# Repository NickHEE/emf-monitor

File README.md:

# emf-monitor
BCIT Capstone Project - BC Hydro

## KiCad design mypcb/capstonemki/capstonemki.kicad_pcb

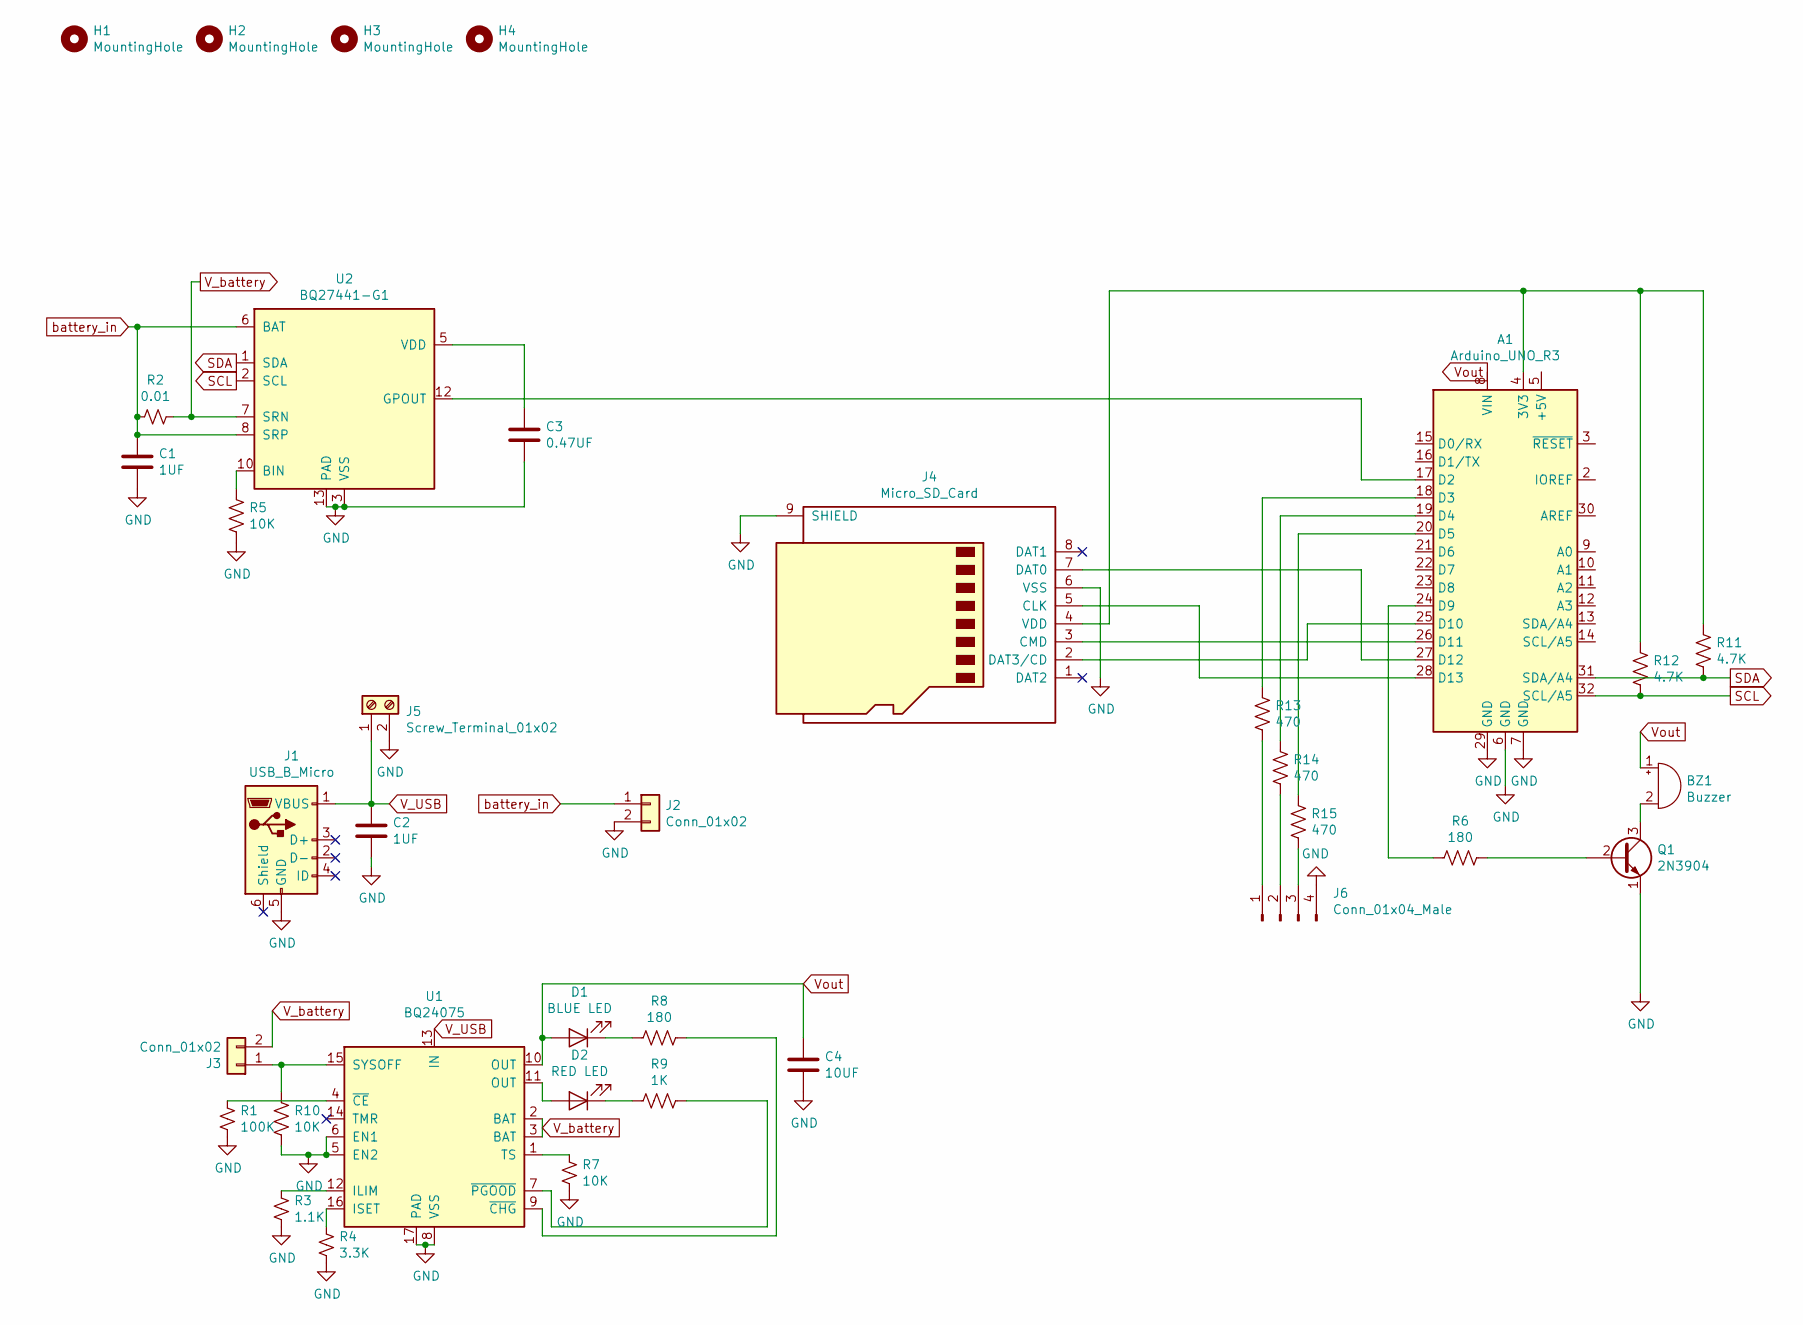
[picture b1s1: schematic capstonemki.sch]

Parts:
A1: Arduino_UNO_R3
BZ1: Buzzer; MagneticBuzzer_ProSignal_ABT-410-RC
C1, C2: 1UF; C_0603_1608Metric
C3: 0.47UF; C_0603_1608Metric
C4: 10UF; C_0603_1608Metric
D1: BLUE LED; LED_0603_1608Metric
D2: RED LED; LED_0603_1608Metric
H1, H2, H3, H4: MountingHole; MountingHole_2.2mm_M2
J1: USB_B_Micro; USB_Micro-B_Molex-105017-0001
J2: Conn_01x02; JST_PH_B2B-PH-K_1x02_P2.00mm_Vertical
J3: Conn_01x02; PinHeader_1x02_P2.54mm_Vertical
J4: Micro_SD_Card; microSD_HC_Molex_104031-0811
J5: Screw_Terminal_01x02; TerminalBlock_bornier-2_P5.08mm
J6: Conn_01x04_Male; PinHeader_1x04_P2.54mm_Vertical
Q1: 2N3904; TO-92_Inline
R1: 100K; R_0603_1608Metric
R2: 0.01; R_0603_1608Metric
R3: 1.1K; R_0603_1608Metric
R4: 3.3K; R_0603_1608Metric
R5, R7, R10: 10K; R_0603_1608Metric
R6, R8: 180; R_0603_1608Metric
R9: 1K; R_0603_1608Metric
R11, R12: 4.7K; R_0603_1608Metric
R13, R14, R15: 470; R_Axial_DIN0309_L9.0mm_D3.2mm_P12.70mm_Horizontal
U1: BQ24075; QFN-16-1EP_3x3mm_P0.5mm_EP1.7x1.7mm
U2: BQ27441-G1; Texas_S-PDSO-N12

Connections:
GND: A1.6 (GND), A1.7 (GND), A1.29 (GND), C1.2, C2.2, C3.2, C4.2, J1.5 (GND), J2.2, J4.6 (VSS), J4.9 (SHIELD), J5.2, J6.4, Q1.1 (E), R1.2, R3.2, R4.2, R5.2, R7.2, R10.2, U1.5 (EN2), U1.6 (EN1), U1.8 (VSS), U1.17 (PAD), U2.3 (VSS), U2.13 (PAD)
unnamed: A1.4 (3V3), J4.4 (VDD), R11.1, R12.2
unnamed: A1.17 (D2), U2.12 (GPOUT)
unnamed: A1.18 (D3), R13.1
unnamed: A1.19 (D4), R14.1
unnamed: A1.20 (D5), R15.1
unnamed: A1.24 (D9), R6.2
unnamed: A1.25 (D10), J4.2 (DAT3/CD)
unnamed: A1.26 (D11), J4.3 (CMD)
unnamed: A1.27 (D12), J4.7 (DAT0)
unnamed: A1.28 (D13), J4.5 (CLK)
unnamed: BZ1.2 (+), Q1.3 (C)
unnamed: C3.1, U2.5 (VDD)
unnamed: D1.1 (K), R8.2
unnamed: D2.1 (K), R9.2
unnamed: D2.2 (A), U1.11 (OUT)
unnamed: J3.1, R10.1, U1.15 (SYSOFF)
unnamed: J6.1, R13.2
unnamed: J6.2, R14.2
unnamed: J6.3, R15.2
unnamed: Q1.2 (B), R6.1
unnamed: R1.1, U1.4 (~CE)
unnamed: R3.1, U1.12 (ILIM)
unnamed: R4.1, U1.16 (ISET)
unnamed: R5.1, U2.10 (BIN)
unnamed: R7.1, U1.1 (TS)
unnamed: R8.1, U1.9 (~CHG)
unnamed: R9.1, U1.7 (~PGOOD)
SCL: A1.32 (SCL/A5), R12.1, U2.2 (SCL)
SDA: A1.31 (SDA/A4), R11.2, U2.1 (SDA)
V_USB: C2.1, J1.1 (VBUS), J5.1, U1.13 (IN)
V_battery: J3.2, R2.1, U1.2 (BAT), U1.3 (BAT), U2.7 (SRN)
Vout: A1.8 (VIN), BZ1.1 (-), C4.1, D1.2 (A), U1.10 (OUT)
battery_in: C1.1, J2.1, R2.2, U2.6 (BAT), U2.8 (SRP)

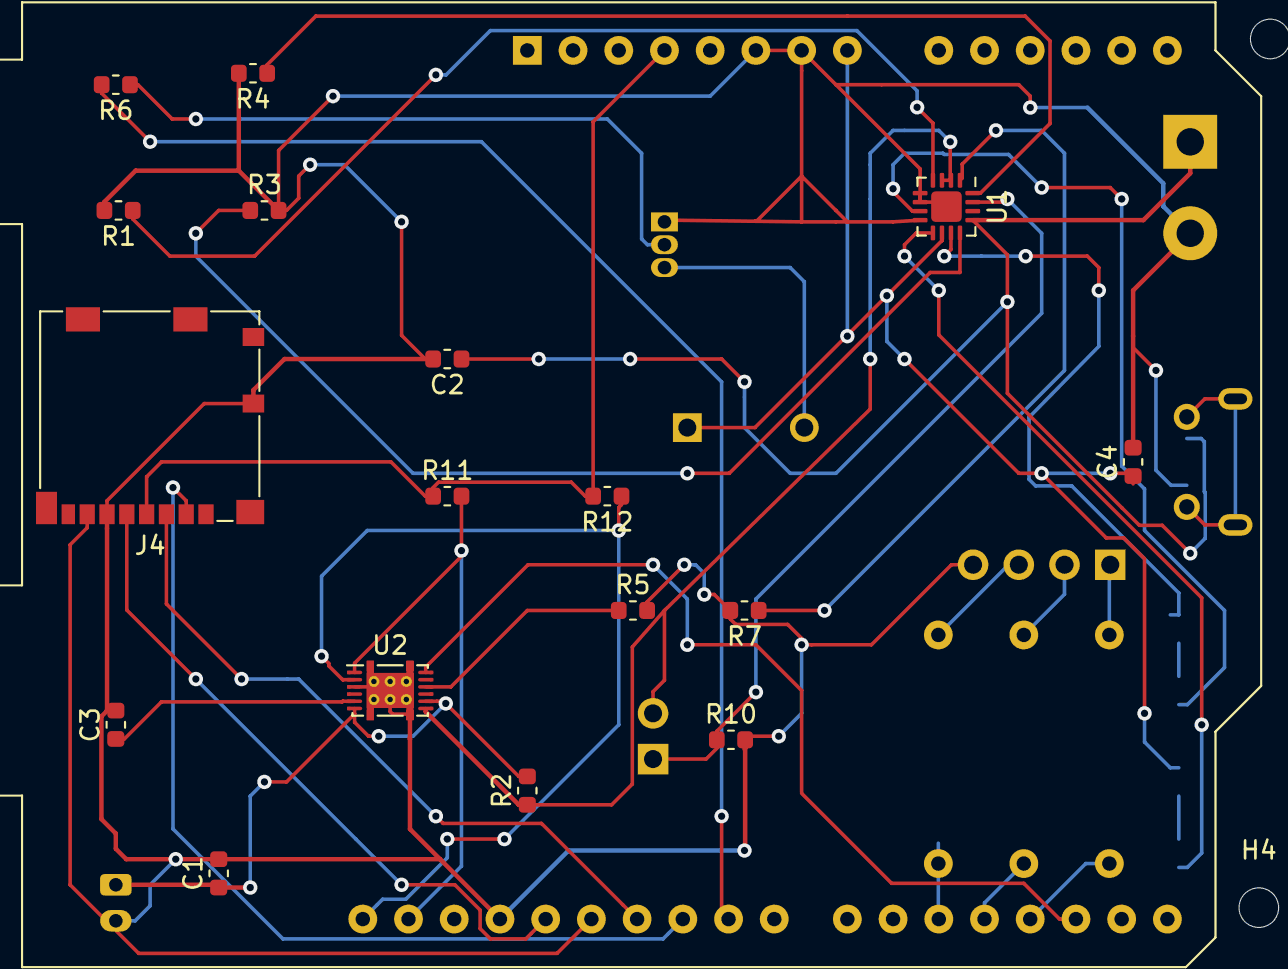
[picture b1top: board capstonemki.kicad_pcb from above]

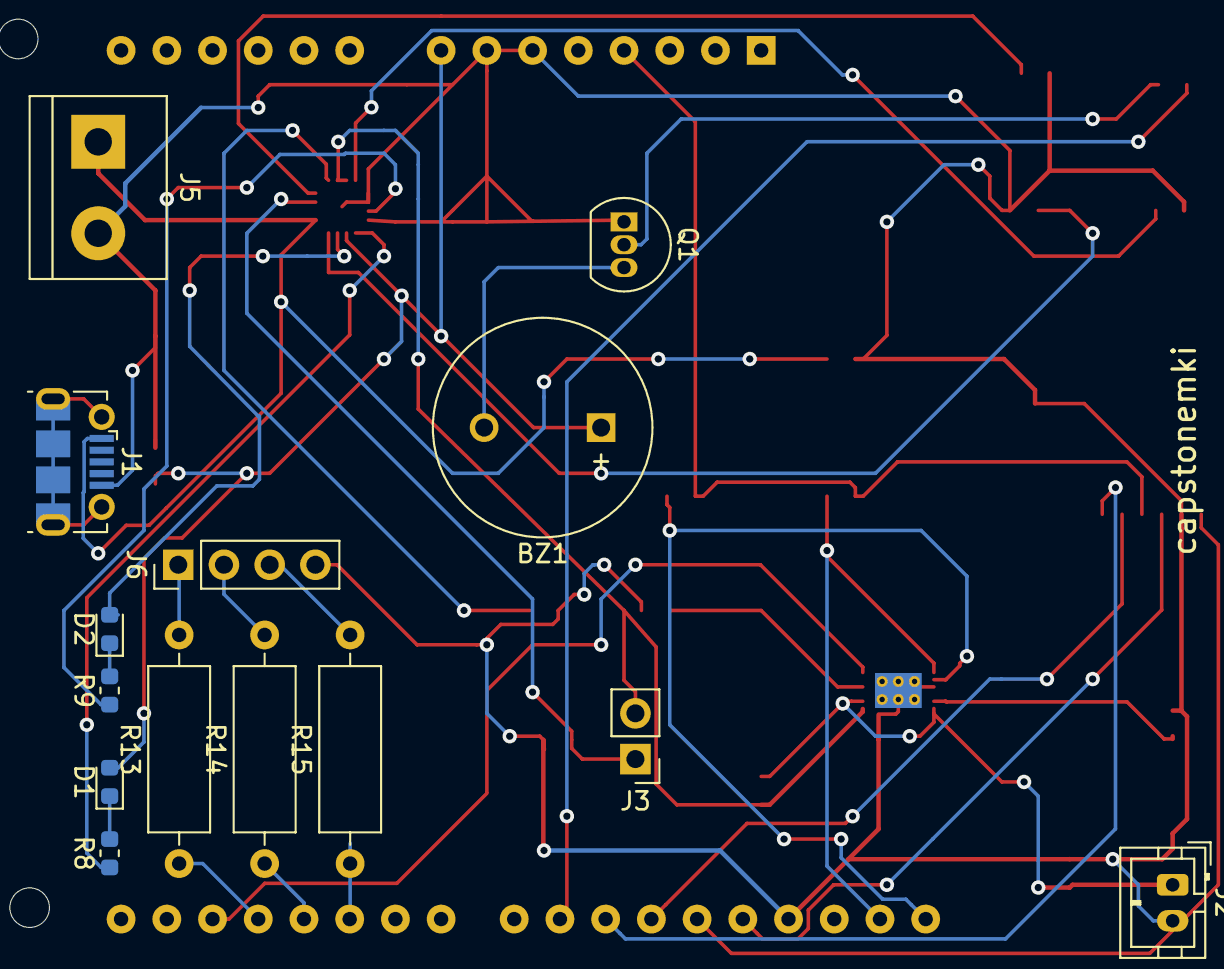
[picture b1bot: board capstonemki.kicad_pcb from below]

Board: 2 copper layers, 36 parts (14 on the bottom side), 34 nets.

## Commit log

2020-01-10 its over bros..
2020-01-16 I love threads
2020-01-23 Filter bros
2020-01-24 added filter
2020-01-29 MBED Project structure
2020-01-30 Merged new project structure with screen code
2020-01-30 Mag sensor
2020-01-31 Start of library code for new sensor
2020-01-31 Mag sensor library WIP
2020-01-31 mbed
2020-01-31 new sensor
2020-02-01 MMC5603NJ WIP
2020-02-03 Able to get measurements from new sensor
2020-02-03 bros..
2020-02-04 sampling working
2020-02-05 debugging rms
2020-02-05 RMS Fixed
2020-02-06 Merged with joseph GUI
2020-02-06 removed old sensor
2020-02-07 Azure debugging
2020-02-11 new connection string
2020-03-03 Add files via upload
    I love Cheng.
2020-05-05 final version
2020-05-05 final
2020-05-05 updated for report
